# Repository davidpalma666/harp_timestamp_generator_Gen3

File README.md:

# Harp Timestamp Generator Gen3

This device generates programable timestamps to up to 6 harp devices.

Includes an internal battery to increase reliability for long term experiments.

# Licensing

The code, designs, documentation, and photos available in this repository is free: you can redistribute it and/or modify it under the terms of the used license.
Each subdirectory will contain a license or, possibly, a set of licenses if it involves both hardware and software. Check files named LICENSE.

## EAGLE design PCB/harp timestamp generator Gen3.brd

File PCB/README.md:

# Harp Timestamp Generator Gen1

## Licensing

The designs, documentation, and photos available in this repository are free: you can redistribute it and/or modify it under the terms of the used license.
Check file named LICENSE.

Copyright OEPS 2021

<br />This work is licensed under a <a rel="license" href="http://creativecommons.org/licenses/by-nc-sa/3.0/igo/">Creative Commons Attribution-NonCommercial-ShareAlike 3.0 IGO License</a>.

If your are interested in obtaining a license to sell this device, please contact info@oeps.tech

[1]: https://docs.google.com/spreadsheets/d/1aobmmEzBDethzIlrm1eg0eYkBqlyX3s9WbA9KgRwVQI/edit?usp=sharing

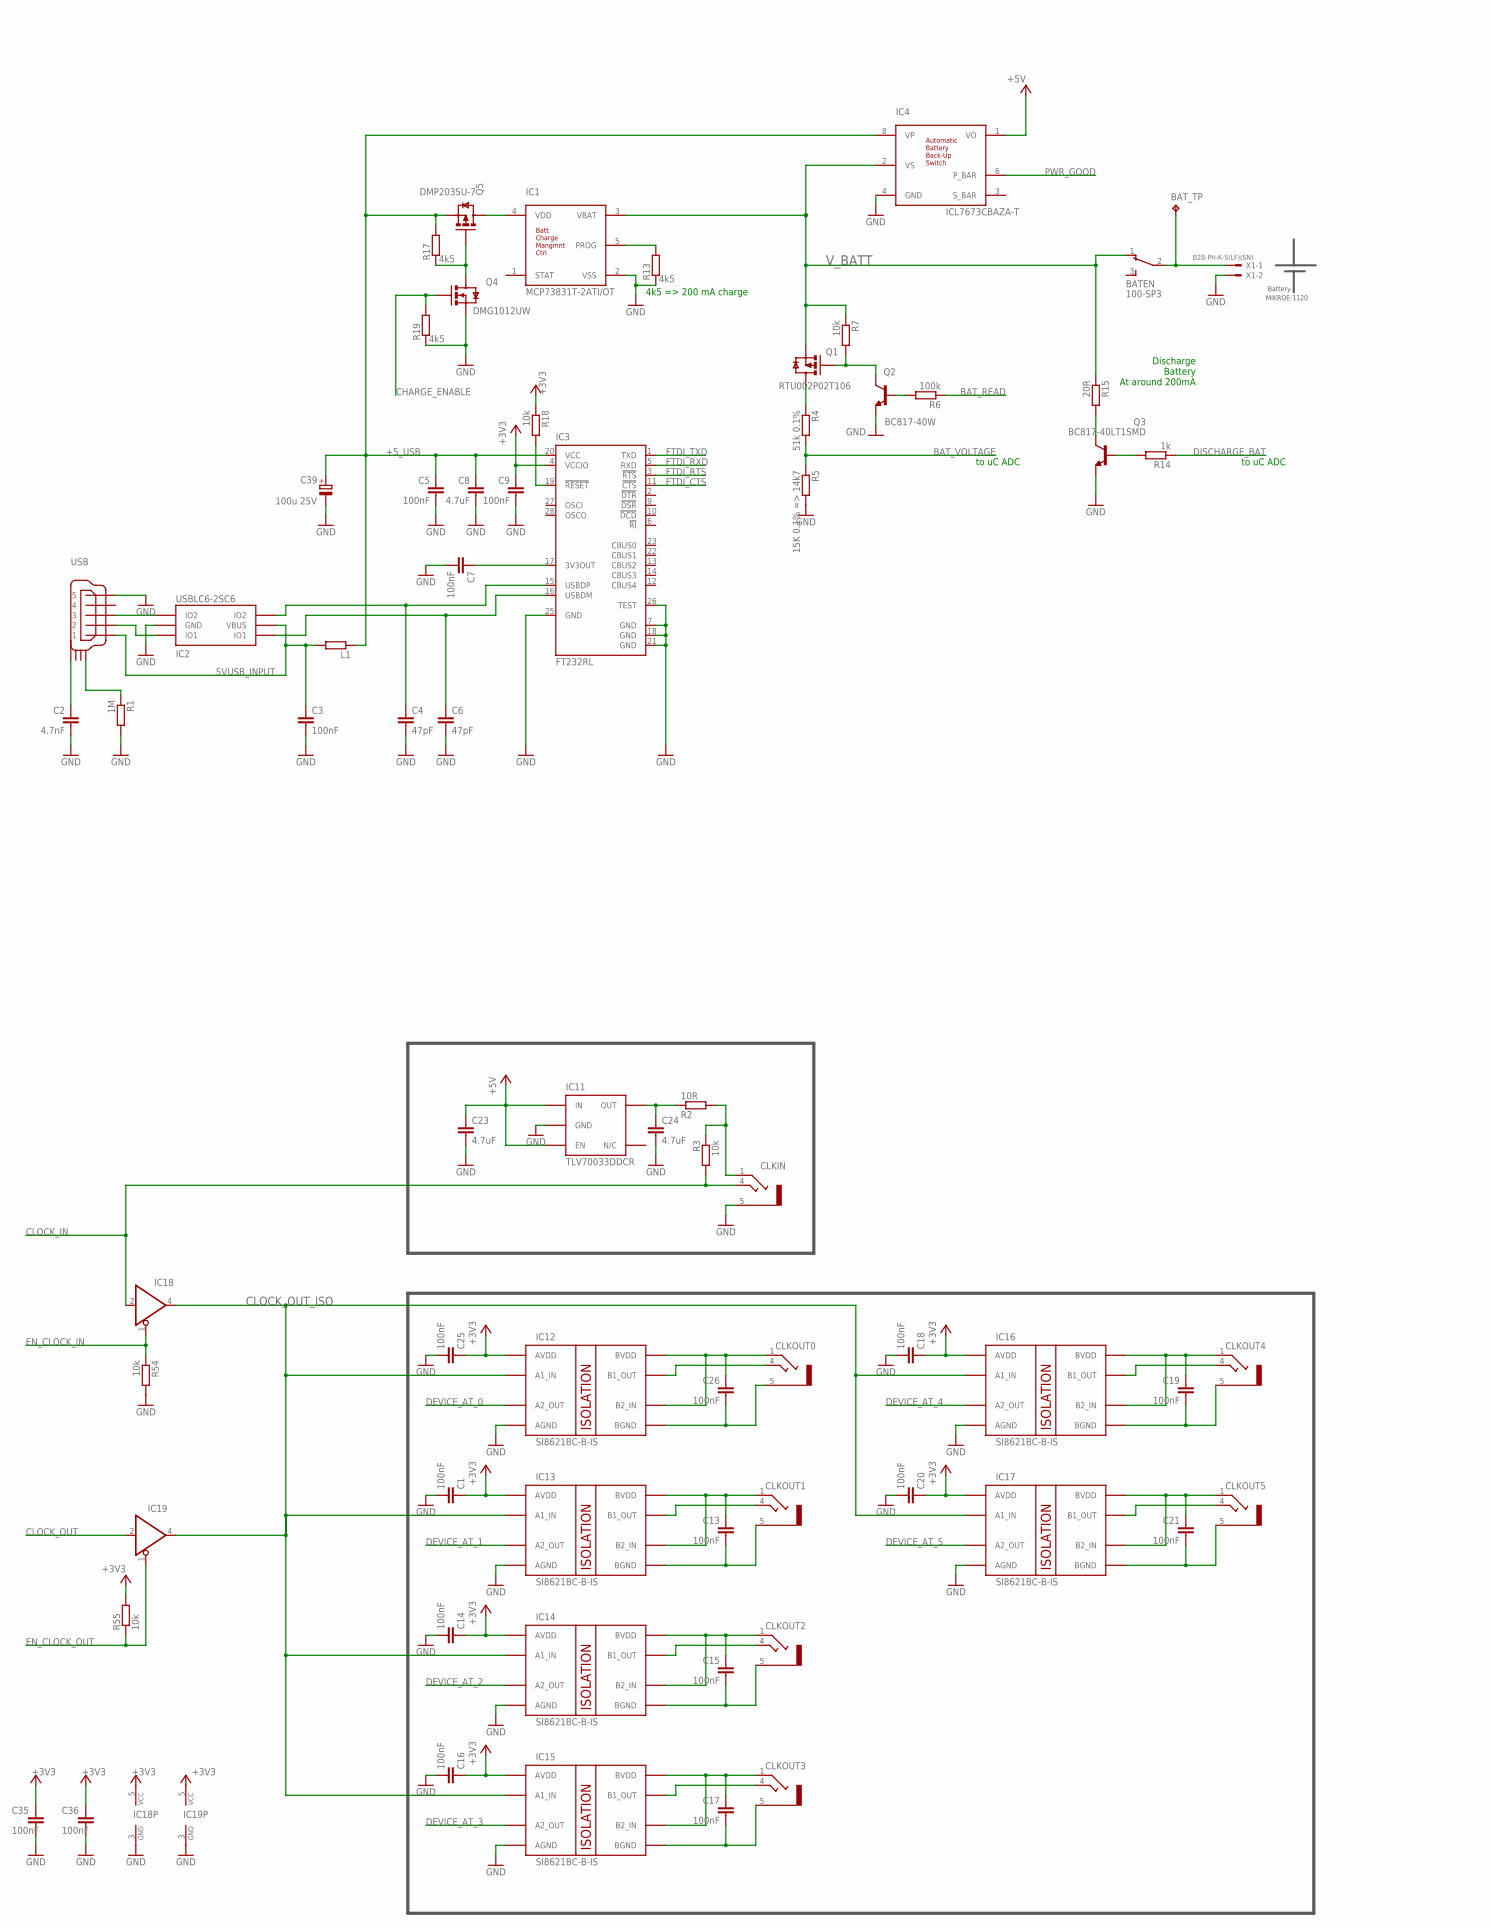
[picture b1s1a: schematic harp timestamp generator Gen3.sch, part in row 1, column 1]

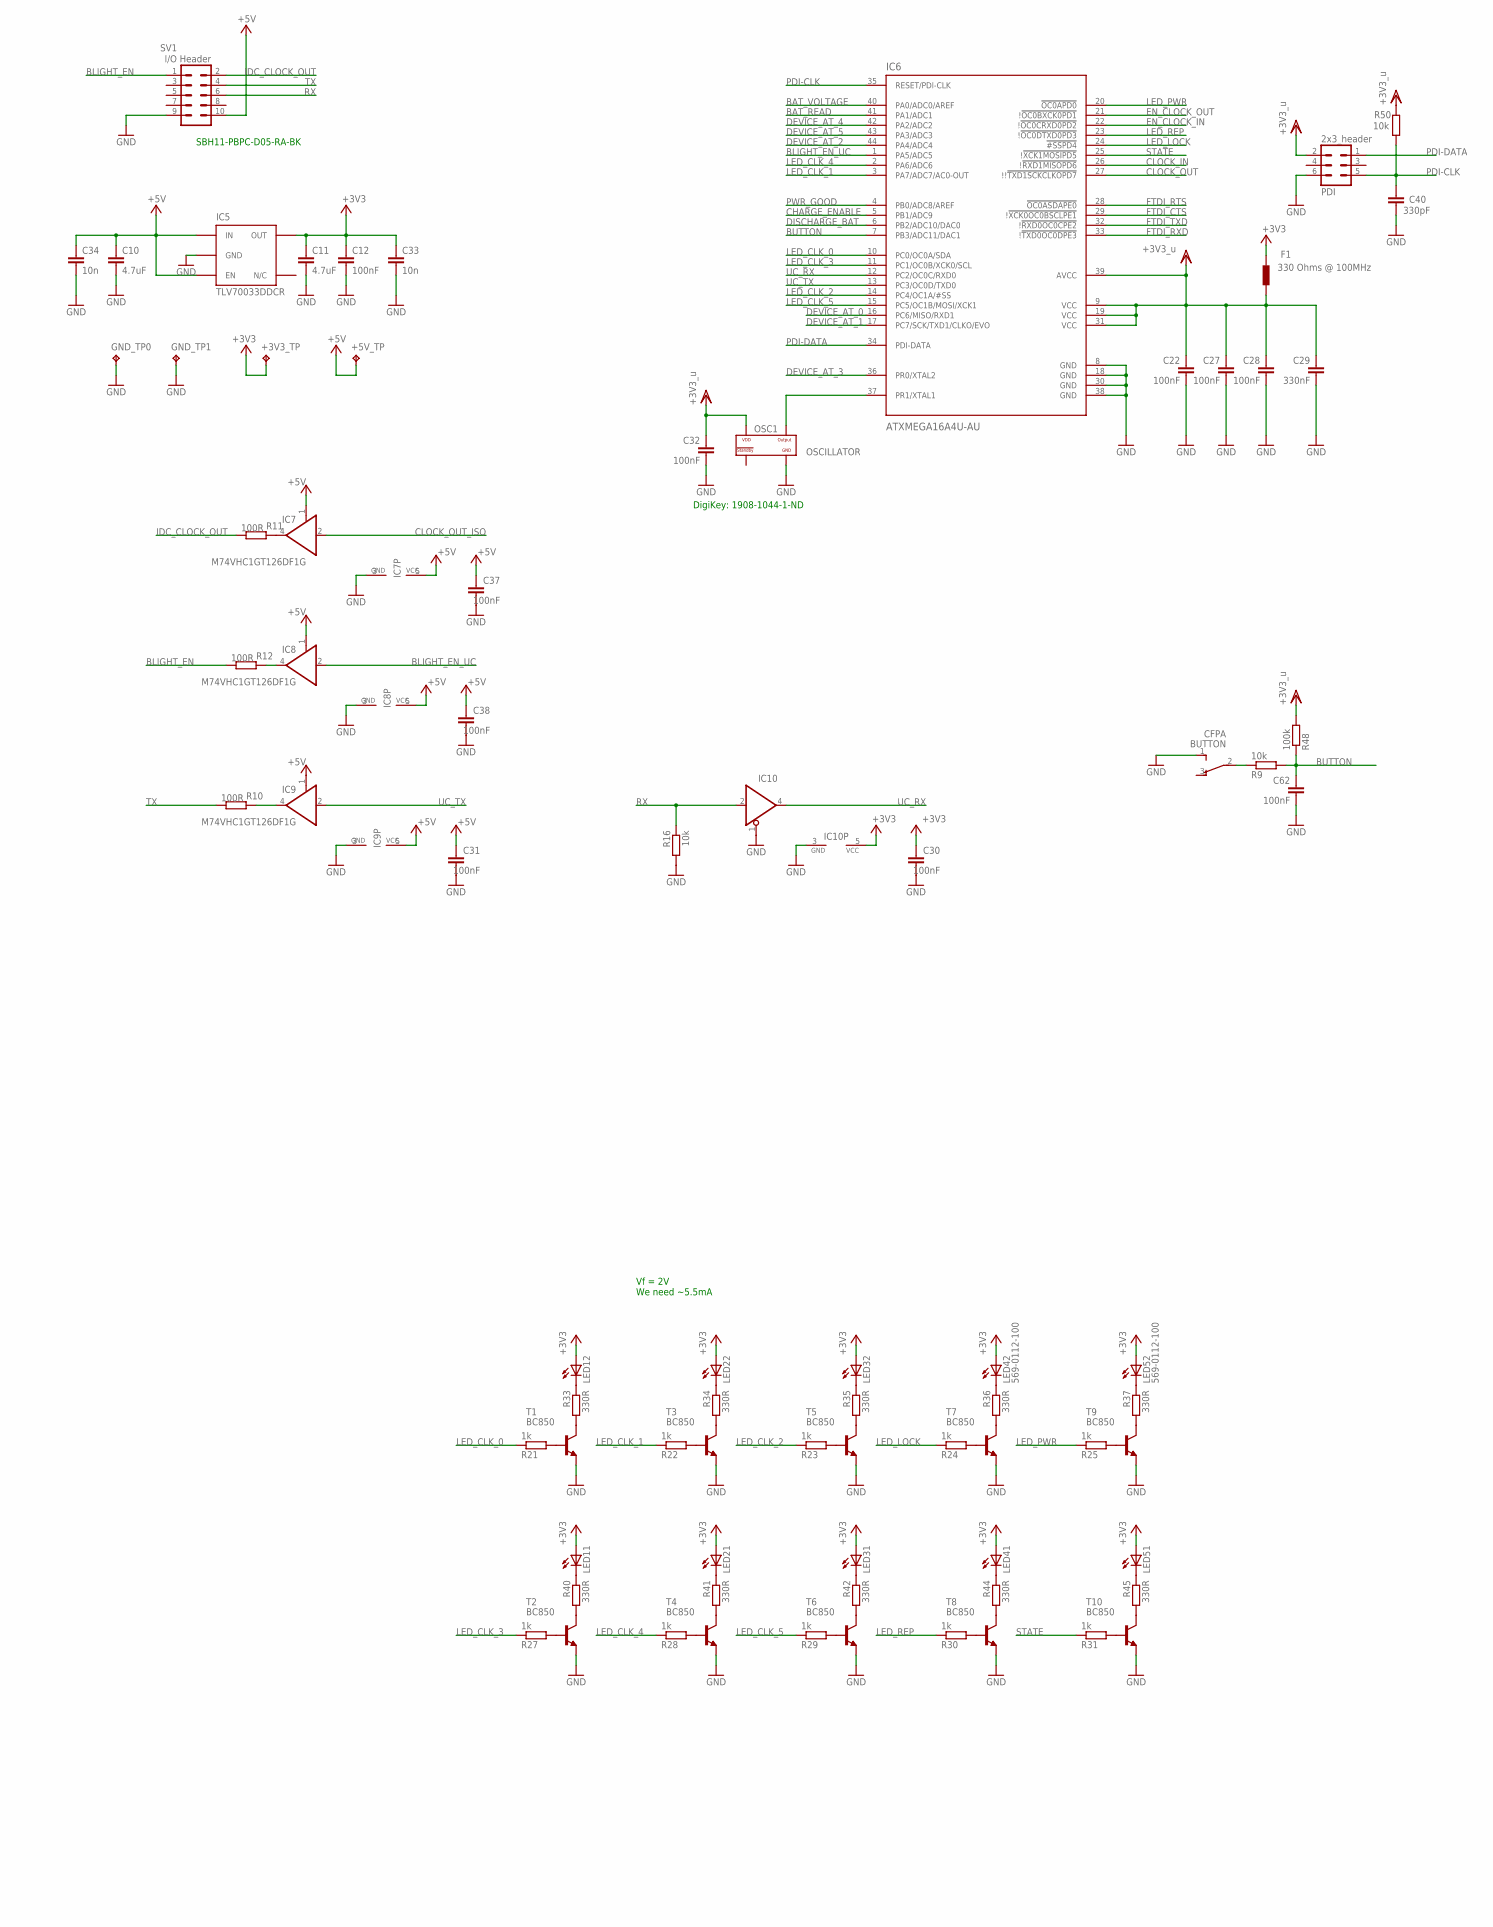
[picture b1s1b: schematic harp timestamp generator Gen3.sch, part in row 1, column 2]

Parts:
+3V3_TP, +5V_TP: TPPAD1-13; P1-13; MPN n.a.
BATEN: 100-SP3; 2M1-SP1-T2-B4-M6RE
BAT_TP: TPPAD1-13; P1-13; MPN n.a.
BUTTON: CFPA; MPN CFPA-1FB4-A2T
C1, C3, C5, C7, C9, C12, C13, C14, C15, C16, C17, C18, C19, C20, C21, C22, C25, C26, C27, C28, C30, C31, C32, C35, C36, C37, C38, C62: 100nF; C0402; MPN CGA2B3X7R1H104K050BB
C2: 4.7nF; C0402; MPN UMK105B7472KV-F
C4, C6: 47pF; C0402; MPN 04025A470JAT2A
C8, C10, C11, C23, C24: 4.7uF; C0603; MPN EMK107ABJ475KA-T
C29: 330nF; C0402; MPN GRM155R61A334KE15D
C33, C34: 10n; C0402; MPN CL05B103KB5NNNC
C39: 100u 25V; TT2D6; MPN EEUFM1E101B
C40: 330pF; C0402; MPN C0402C331J5GACTU
CLKIN: CLCK_JACK; 35RASMT2BHNTRX; MPN 35RASMT2BHNTRX
CLKOUT0, CLKOUT1, CLKOUT2, CLKOUT3, CLKOUT4, CLKOUT5: CLCK_JACK; 35RASMT2BHNTRX; MPN 35RASMT2BHNTRX
F1: 330 Ohms @ 100MHz; R0603; MPN BLM18SG331TN1D
GND_TP0, GND_TP1: TPPAD1-13; P1-13; MPN n.a.
IC1: MCP73831T-2ATI/OT; TSOT23-5
IC2: USBLC6-2SC6; SOT23-6L; MPN USBLC6-2SC6
IC3: FT232RL; SSOP28; MPN FT232RL-REEL
IC4: ICL7673CBAZA-T; SOIC8; MPN ICL7673CBAZA-T
IC5, IC11: TLV70033DDCR; TSOT23-5; MPN TLV70033DDCR
IC6: ATXMEGA16A4U-AU; QFP80P1200X1200X120-44N; MPN ATXMEGA16A4U-AU
IC7, IC8, IC9: M74VHC1GT126DF1G; SC70-5; MPN M74VHC1GT126DF1G
IC10, IC18, IC19: SN74LVC1G125DBVT; SOT23-5; MPN SN74LVC1G125DBVT
IC12, IC13, IC14, IC15, IC16, IC17: SI8621BC-B-IS; SOIC8; MPN Si8621BC-B-IS
L1: 40R@100MHz; R0805; MPN MI0805K400R-10
LED1, LED2, LED3, LED4, LED5: 569-0112-100; 569-011X-X00_LED_ARRAY; MPN 5690-111-100F
OSC1: OSCILLATOR; OSCILLATOR_3.2X2.5; MPN O 32,0-JT32C-A-K-3,3-LF
PDI: 2x3_header; MA03-2; MPN 67996-206HLF
Q1: RTU002P02T106; SOT323; MPN RTU002P02T106
Q2: BC817-40W; SOT323-BEC; MPN BC817-40W,135
Q3: BC817-40LT1SMD; SOT23-BEC; MPN SBC817-40LT1G
Q4: DMG1012UW; SOT323; MPN DMG1012UW-7
Q5: DMP2035U-7; SOT323
R1: 1M; R0402; MPN CRCW04021M00FKEDC
R2: 10R; R0402; MPN CRCW040210R0FKEDHP
R3, R7, R9, R16, R18: 10k; R0402; MPN CRCW040210K0FKEDC
R4: 51k 0.1%; R0402; MPN ERA-2AEB513X
R5: 15K 0.1% => 14k7; R0402; MPN RT0402BRD0714K7L
R6, R48: 100k; R0402; MPN ERJ-2RHD1002X
R10, R11, R12: 100R; R0603; MPN RT0603DRD07100RL
R13, R17, R19: 4k5; R0402; MPN RT0402BRD074K53L
R14: 1k; R0402; MPN CRCW040210K0FKEDC
R15: 20R; R2512; MPN RCP2512W25R0GEB
R21, R22, R23, R24, R25, R27, R28, R29, R30, R31: 1k; R0402; MPN CRCW04021K00FKEDHP
R33, R34, R35, R36, R37, R40, R41, R42, R44, R45: 330R; R0402; MPN RC0402FR-07330RL
R50: 10k; R0402; MPN CRCW040210K0FKED
R54, R55: 10k; R0402; MPN CRCW04021K00FKEDHP
SV1: I/O Header; ML10L; MPN SBH11-PBPC-D05-RA-BK
T1, T2, T3, T4, T5, T6, T7, T8, T9, T10: BC850; SOT23; MPN BC850C,215
USB: mini USB; 240-0002-1; MPN UX60-MB-5S8
X1: B2B-PH-K-S(LF)(SN); JST-XH-02-PACKAGE-ROUND-PAD; MPN B2B-PH-K-S(LF)(SN)

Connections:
5VUSB_INPUT: C3.1, IC2.P$5 (VBUS), L1.2, USB.P$1 (1)
+3V3: +3V3_TP.TP, C1.1, C9.1, C11.1, C12.1, C14.1, C16.1, C18.1, C20.1, C25.1, C30.1, C33.1, C35.1, C36.1, F1.2, IC3.4 (VCCIO), IC5.5 (OUT), IC10.5 (VCC), IC12.1 (AVDD), IC13.1 (AVDD), IC14.1 (AVDD), IC15.1 (AVDD), IC16.1 (AVDD), IC17.1 (AVDD), IC18.5 (VCC), IC19.5 (VCC), LED1.A1 (A), LED1.A2 (A), LED2.A1 (A), LED2.A2 (A), LED3.A1 (A), LED3.A2 (A), LED4.A1 (A), LED4.A2 (A), LED5.A1 (A), LED5.A2 (A), R18.1, R55.2
+5V: +5V_TP.TP, C10.1, C23.1, C31.1, C34.1, C37.1, C38.1, IC4.1 (VO), IC5.1 (IN), IC5.3 (EN), IC7.1 (OE), IC7.5 (VCC), IC8.1 (OE), IC8.5 (VCC), IC9.1 (OE), IC9.5 (VCC), IC11.1 (IN), IC11.3 (EN), SV1.10
+5_USB: C5.1, C8.1, C39.+, IC3.20 (VCC), IC4.8 (VP), L1.1, Q5.1 (S), R17.2
BAT_READ: IC6.41 (PA1/ADC1), R6.1
BAT_VOLTAGE: IC6.40 (PA0/ADC0/AREF), R4.2, R5.1
BLIGHT_EN: R12.1, SV1.1
BLIGHT_EN_UC: IC6.1 (PA5/ADC5), IC8.2 (I)
BUTTON: C62.1, IC6.7 (PB3/ADC11/DAC1), R9.2, R48.1
CHARGE_ENABLE: IC6.5 (PB1/ADC9), Q4.2 (G), R19.2
CLKOUT0: CLKOUT0.4, IC12.7 (B1_OUT)
CLKOUT1: CLKOUT1.4, IC13.7 (B1_OUT)
CLKOUT2: CLKOUT2.4, IC14.7 (B1_OUT)
CLKOUT3: CLKOUT3.4, IC15.7 (B1_OUT)
CLKOUT4: CLKOUT4.4, IC16.7 (B1_OUT)
CLKOUT5: CLKOUT5.4, IC17.7 (B1_OUT)
CLOCK_IN: CLKIN.4, IC6.26 (!!RXD1MISOPD6), IC18.2 (I), R3.2
CLOCK_OUT: IC6.27 (!!!TXD1SCKCLKOPD7), IC19.2 (I)
CLOCK_OUT_ISO: IC7.2 (I), IC12.2 (A1_IN), IC13.2 (A1_IN), IC14.2 (A1_IN), IC15.2 (A1_IN), IC16.2 (A1_IN), IC17.2 (A1_IN), IC18.4 (O), IC19.4 (O)
DEVICE_AT_0: IC6.16 (PC6/MISO/RXD1), IC12.3 (A2_OUT)
DEVICE_AT_1: IC6.17 (PC7/SCK/TXD1/CLKO/EVO), IC13.3 (A2_OUT)
DEVICE_AT_2: IC6.44 (PA4/ADC4), IC14.3 (A2_OUT)
DEVICE_AT_3: IC6.36 (PR0/XTAL2), IC15.3 (A2_OUT)
DEVICE_AT_4: IC6.42 (PA2/ADC2), IC16.3 (A2_OUT)
DEVICE_AT_5: IC6.43 (PA3/ADC3), IC17.3 (A2_OUT)
DISCHARGE_BAT: IC6.6 (PB2/ADC10/DAC0), R14.1
EN_CLOCK_IN: IC6.22 (!!OC0CRXD0PD2), IC18.1 (OE), R54.1
EN_CLOCK_OUT: IC6.21 (!!OC0BXCK0PD1), IC19.1 (OE), R55.1
FTDI_CTS: IC3.11 (!CTS), IC6.29 (!!XCK0OC0BSCLPE1)
FTDI_RTS: IC3.3 (!RTS), IC6.28 (!OC0ASDAPE0)
FTDI_RXD: IC3.5 (RXD), IC6.33 (!!TXD0OC0DPE3)
FTDI_TXD: IC3.1 (TXD), IC6.32 (!!RXD0OC0CPE2)
GND: BUTTON.1 (3), C1.2, C2.2, C3.2, C4.2, C5.2, C6.2, C7.2, C8.2, C9.2, C10.2, C11.2, C12.2, C14.2, C16.2, C18.2, C20.2, C22.2, C23.2, C24.2, C25.2, C27.2, C28.2, C29.2, C30.2, C31.2, C32.2, C33.2, C34.2, C35.2, C36.2, C37.2, C38.2, C39.-, C40.2, C62.2, CLKIN.5, GND_TP0.TP, GND_TP1.TP, IC1.2 (VSS), IC2.P$2 (GND), IC3.7 (GND), IC3.18 (GND), IC3.21 (GND), IC3.25 (GND), IC3.26 (TEST), IC4.4 (GND), IC5.2 (GND), IC6.8 (GND), IC6.18 (GND), IC6.30 (GND), IC6.38 (GND), IC7.3 (GND), IC8.3 (GND), IC9.3 (GND), IC10.1 (OE), IC10.3 (GND), IC11.2 (GND), IC12.4 (AGND), IC13.4 (AGND), IC14.4 (AGND), IC15.4 (AGND), IC16.4 (AGND), IC17.4 (AGND), IC18.3 (GND), IC19.3 (GND), OSC1.P$2 (GND), PDI.6, Q2.E, Q3.E, Q4.1 (S), R1.2, R5.2, R13.1, R16.2, R19.1, R54.2, SV1.9, T1.2 (E), T2.2 (E), T3.2 (E), T4.2 (E), T5.2 (E), T6.2 (E), T7.2 (E), T8.2 (E), T9.2 (E), T10.2 (E), USB.P$5 (5), X1.2
GND_ISO: C26.2, CLKOUT0.5, IC12.5 (BGND)
GND_ISO1: C13.2, CLKOUT1.5, IC13.5 (BGND)
GND_ISO2: C15.2, CLKOUT2.5, IC14.5 (BGND)
GND_ISO3: C17.2, CLKOUT3.5, IC15.5 (BGND)
GND_ISO4: C19.2, CLKOUT4.5, IC16.5 (BGND)
GND_ISO5: C21.2, CLKOUT5.5, IC17.5 (BGND)
IDC_CLOCK_OUT: R11.1, SV1.2
LED_CLK_0: IC6.10 (PC0/OC0A/SDA), R21.1
LED_CLK_1: IC6.3 (PA7/ADC7/AC0-OUT), R22.1
LED_CLK_2: IC6.14 (PC4/OC1A/#SS), R23.1
LED_CLK_3: IC6.11 (PC1/OC0B/XCK0/SCL), R27.1
LED_CLK_4: IC6.2 (PA6/ADC6), R28.1
LED_CLK_5: IC6.15 (PC5/OC1B/MOSI/XCK1), R29.1
LED_LOCK: IC6.24 (!#SSPD4), R24.1
LED_PWR: IC6.20 (!OC0APD0), R25.1
LED_REP: IC6.23 (!!OC0DTXD0PD3), R30.1
unnamed: R24.2, T7.1 (B)
unnamed: Q4.3 (D), Q5.2 (G), R17.1
unnamed: IC8.4 (O), R12.2
unnamed: IC9.4 (O), R10.2
unnamed: C26.1, CLKOUT0.1, IC12.6 (B2_IN), IC12.8 (BVDD)
unnamed: C13.1, CLKOUT1.1, IC13.6 (B2_IN), IC13.8 (BVDD)
unnamed: R36.2, T7.3 (C)
unnamed: IC7.4 (O), R11.2
unnamed: IC1.4 (VDD), Q5.3 (D)
unnamed: C15.1, CLKOUT2.1, IC14.6 (B2_IN), IC14.8 (BVDD)
unnamed: R22.2, T3.1 (B)
unnamed: IC1.5 (PROG), R13.2
unnamed: R21.2, T1.1 (B)
unnamed: LED3.C1 (C), R42.1
unnamed: R33.2, T1.3 (C)
unnamed: R27.2, T2.1 (B)
unnamed: R34.2, T3.3 (C)
unnamed: R40.2, T2.3 (C)
unnamed: LED3.C2 (C), R35.1
unnamed: R28.2, T4.1 (B)
unnamed: R41.2, T4.3 (C)
unnamed: R23.2, T5.1 (B)
unnamed: R35.2, T5.3 (C)
unnamed: R29.2, T6.1 (B)
unnamed: R42.2, T6.3 (C)
unnamed: LED1.C2 (C), R33.1
unnamed: LED2.C2 (C), R34.1
unnamed: LED1.C1 (C), R40.1
unnamed: LED2.C1 (C), R41.1
unnamed: R30.2, T8.1 (B)
unnamed: Q3.B, R14.2
unnamed: Q3.C, R15.2
unnamed: C17.1, CLKOUT3.1, IC15.6 (B2_IN), IC15.8 (BVDD)
unnamed: C7.1, IC3.17 (3V3OUT)
unnamed: IC2.P$1 (IO1), USB.P$2 (2)
unnamed: CLKIN.1, R2.2, R3.1
unnamed: C24.1, IC11.5 (OUT), R2.1
unnamed: BUTTON.2, R9.1
unnamed: C19.1, CLKOUT4.1, IC16.6 (B2_IN), IC16.8 (BVDD)
unnamed: R44.2, T8.3 (C)
unnamed: C21.1, CLKOUT5.1, IC17.6 (B2_IN), IC17.8 (BVDD)
unnamed: IC2.P$3 (IO2), USB.P$3 (3)
unnamed: R25.2, T9.1 (B)
unnamed: R37.2, T9.3 (C)
unnamed: R31.2, T10.1 (B)
unnamed: C2.1, USB.SHIELD_4
unnamed: R45.2, T10.3 (C)
unnamed: R1.1, USB.SHIELD_1
unnamed: LED5.C1 (C), R45.1
unnamed: LED5.C2 (C), R37.1
unnamed: LED4.C2 (C), R36.1
unnamed: LED4.C1 (C), R44.1
unnamed: BATEN.2, BAT_TP.TP, X1.1
unnamed: Q1.3 (D), R4.1
unnamed: Q1.2 (G), Q2.C, R7.2
unnamed: Q2.B, R6.2
unnamed: IC3.19 (!RESET), R18.2
OSC1: IC6.37 (PR1/XTAL1), OSC1.P$3 (OUTPUT)
PDI-CLK: C40.1, IC6.35 (RESET/PDI-CLK), PDI.5, R50.1
PDI-DATA: IC6.34 (PDI-DATA), PDI.1
PWR_GOOD: IC4.6 (P_BAR), IC6.4 (PB0/ADC8/AREF)
RX: IC10.2 (I), R16.1, SV1.6
STATE: IC6.25 (!!XCK1MOSIPD5), R31.1
TX: R10.1, SV1.4
UC_RX: IC6.12 (PC2/OC0C/RXD0), IC10.4 (O)
UC_TX: IC6.13 (PC3/OC0D/TXD0), IC9.2 (I)
USBDM: C6.1, IC2.P$6 (IO1), IC3.16 (USBDM)
USBDP: C4.1, IC2.P$4 (IO2), IC3.15 (USBDP)
VDD: C22.1, C27.1, C28.1, C29.1, C32.1, F1.1, IC6.9 (VCC), IC6.19 (VCC), IC6.31 (VCC), IC6.39 (AVCC), OSC1.P$4 (VDD), PDI.2, R48.2, R50.2
V_BATT: BATEN.1, IC1.3 (VBAT), IC4.2 (VS), Q1.1 (S), R7.1, R15.1

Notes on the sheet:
Vf = 2V We need ~5.5mA
SBH11-PBPC-D05-RA-BK
4k5 => 200 mA charge
Battery
to uC ADC
MIKROE-1120
Discharge Battery At around 200mA
DigiKey: 1908-1044-1-ND

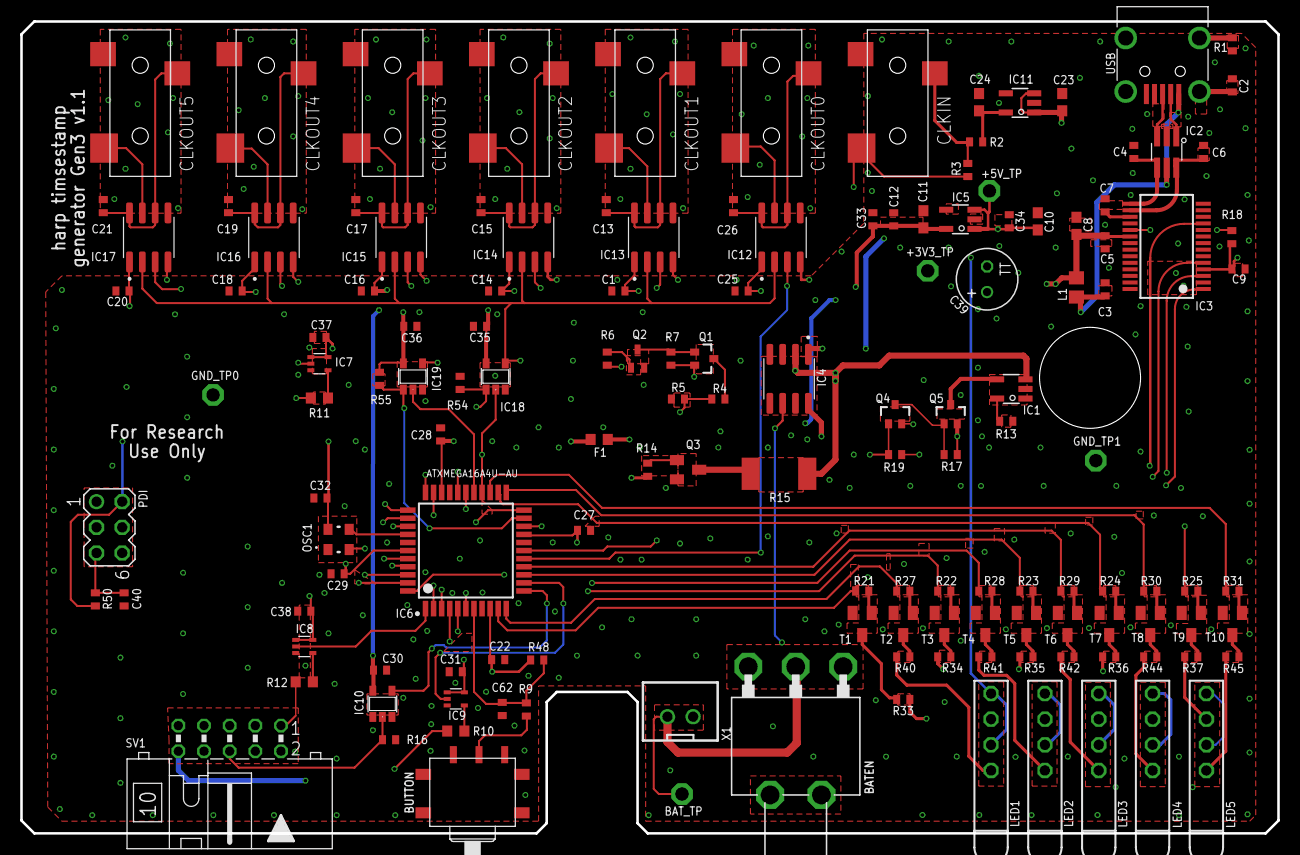
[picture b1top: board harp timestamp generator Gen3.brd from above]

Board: 4 copper layers, 124.5 x 80.4 mm, 143 parts (0 on the bottom side), 119 nets.

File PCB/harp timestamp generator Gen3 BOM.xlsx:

Qty | Value | Package | Parts | MPN | Type | Distributor | Distributor PN
ASSEMBLY HOUSE
1 | CFPA | CFPA | BUTTON | CFPA-1FB4-A2T | SMD | Digikey | 563-1246-1-ND
28 | 100nF | C0402 | C1, C3, C5, C7, C9, C12, C13, C14, C15, C16, C17, C18, C19, C20, C21, C22, C25,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 | CGA2B3X7R1H104K050BB | SMD | Digikey | 445-6899-1-ND
5 | 4.7uF | C0603 | C8, C10, C11, C23, C24 | CRCW040210R0FKEDHP | SMD | Digikey | 541-10.0YCT-ND
1 | 4.7nF | C0402 | C2 | UMK105B7472KV-F | SMD | Digikey | 587-2237-1-ND
1 | 330nF | C0402 | C29 | GRM155R61A334KE15D | SMD | Digikey | 490-3263-1-ND
2 | 10n | C0402 | C33, C34 | CL05B103KB5NNNC | SMD | Digikey | 1276-1028-1-ND
2 | 47pF | C0402 | C4, C6 | 06035A470JAT2A | SMD | Digikey | 478-1171-1-ND
1 | 100u 25V | TT2D6 | C39 | EEUFM1E101B | TH | Digikey | P19702CT-ND
1 | 330pF | C0402 | C40 | C0402C331J5GACTU | SMD | Digikey | 399-7787-1-ND
7 | CLCK_JACK | 35RASMT2BHNTRX | CLKIN, CLKOUT0, CLKOUT1, CLKOUT2, CLKOUT3, CLKOUT4, CLKOUT5 | 35RASMT2BHNTRX | SMD | Digikey | SC1489-1-ND
1 | 330 Ohms @ 100MHz | R0603 | F1 | BLM18SG331TN1D | SMD | Digikey | 490-3997-1-ND
1 | MCP73831T-2ATI/OT | TSOT23-5 | IC1 | MCP73831T-2ATI/OT | SMD | Digikey | MCP73831T-2ATI/OTCT-ND
3 | SN74LVC1G125DBVT | SOT23-5 | IC10, IC18, IC19 | SN74LVC1G125DBVT | SMD | Digikey | 296-26595-1-ND
6 | SI8621BC-B-IS | SOIC8 | IC12, IC13, IC14, IC15, IC16, IC17 | Si8621BC-B-IS | SMD | Digikey | 336-2064-5-ND | Replacements: SI8621BB-B-IS
1 | USBLC6-2SC6 | SOT23-6L | IC2 | USBLC6-2SC6 | SMD | Digikey | 497-5235-1-ND
1 | FT232RL | SSOP28 | IC3 | FT232RL-REEL | SMD | Digikey | 768-1007-1-ND
1 | ICL7673CBAZA-T | SOIC8 | IC4 | ICL7673CBAZA-T | SMD | Digikey | ICL7673CBAZA-TCT-ND
2 | TLV70033DDCR | TSOT23-5 | IC5, IC11 | TLV70033DDCR | SMD | Digikey | 296-27937-6-ND
1 | ATXMEGA16A4U-AU | QFP80P1200X1200X120-44N | IC6 | ATXMEGA16A4U-AU | SMD | Digikey | ATXMEGA16A4U-AU-ND
3 | M74VHC1GT126DF1G | SC70-5 | IC7, IC8, IC9 | M74VHC1GT126DF1G | SMD | Digikey | M74VHC1GT126DF1GOSCT-ND
1 | 40R@100MHz | R0805 | L1 | MI0805K400R-10 | SMD | Digikey | 240-2389-1-ND
5 | 569-0112-100 | 569-011X-X00_LED_ARRAY | LED1, LED2, LED3, LED4, LED5 | 5690-111-100F | SMD | Digikey | 350-1782-ND
1 | OSCILLATOR | OSCILLATOR_3.2X2.5 | OSC1 | O 32,0-JT32C-A-K-3,3-LF | SMD | Digikey | 1908-1044-1-ND
1 | 2x3_header | MA03-2 | PDI | 67996-206HLF | TH | Digikey | 609-3210-ND
1 | RTU002P02T106 | SOT323 | Q1 | RTU002P02T106 | SMD | Digikey | RTU002P02T106CT-ND
1 | BC817-40W | SOT323-BEC | Q2 | BC817-40W,135 | SMD | Digikey | 1727-6185-1-ND
1 | BC817-40LT1SMD | SOT23-BEC | Q3 | SBC817-40LT1G | SMD | Digikey | SBC817-40LT1GOSCT-ND
1 | DMG1012UW | SOT323 | Q4 | DMG1012UW-7 | SMD | Digikey | DMG1012UW-7DICT-ND
1 | DMP2035U-7 | SOT323 | Q5 | DMP2035U-7 | SMD | Digikey | DMP2035U-7DICT-ND
1 | 1M | R0402 | R1 | CRCW04021M00FKEDC | SMD | Digikey | DMP2035U-7
3 | 100R | R0603 | R10, R11, R12 | RT0603DRD07100RL | SMD | Digikey | 311-100DCT-ND
3 | 4k5 | R0402 | R13, R17, R19 | RT0402BRD074K53L | SMD | Digikey | YAG1444CT-ND
1 | 20R | R2512 | R15 | CRM2512-FX-20R0ELF | SMD | Digikey | 118-CRM2512-FX-20R0ELFCT-ND
1 | 10R | R0402 | R2 | CRCW040210R0FKEDHP | SMD | Digikey | 541-10.0YCT-ND
13 | 1k | R0402 | R14, R21, R22, R23, R24, R25, R27, R28, R29, R30, R31, R54, R55 | CRCW04021K00FKED | SMD | Digikey | 541-1.00KYCT-ND
6 | 10k | R0402 | R3, R7, R9, R16, R18, R50 | CRCW040210K0FKEDC | SMD | Digikey | 541-3959-1-ND
10 | 330R | R0402 | R33, R34, R35, R36, R37, R40, R41, R42, R44, R45 | RC0402FR-07330RL | SMD | Digikey | 311-330LRCT-ND
1 | 51k 0.1% | R0402 | R4 | ERA-2AEB513X | SMD | Digikey | P51KDCCT-ND
1 | 15K 0.1% => 14k7 | R0402 | R5 | RT0402BRD0714K7L | SMD | Digikey | YAG4174CT-ND
2 | 100k | R0402 | R6, R48 | RC0603FR-07100KL | SMD | Digikey | 311-100KHRCT-ND
1 | 0 | R0402 | R8 | RC0603FR-070RL | SMD | Digikey | 311-0.0HRCT-ND
1 | I/O Header | ML10L | SV1 | SBH11-PBPC-D05-RA-BK | TH | Digikey | S9177-ND
10 | BC850 | SOT23 | T1, T2, T3, T4, T5, T6, T7, T8, T9, T10 | BC850C,215 | SMD | Digikey | 1727-4862-1-ND
1 | mini USB | 240-0002-1 | USB | UX60-MB-5S8 | SMD | Digikey | H2960TR-ND
1 | B2B-PH-K-S(LF)(SN) | JST-XH-02-PACKAGE-ROUND-PAD | X1 | B2B-XH-A(LF)(SN) | SMD | Digikey | 455-2247-ND
POST-PRODUCTION
1 |  |  | Front Panel PCB | PCBWAY
1 |  |  | Rear Panel PCB | PCBWAY
1 |  |  | Enclosure | B5-080BK
1 |  |  | Battery lithium Polymer 2 Ah | MIKROE-1120 | - | Farnell | 2786900
4 |  |  | Bumper Cylindrical Dome 9.53mm | SJ-5306-CLEAR-3000/CASE
ACCESSORIES
3 |  |  | 3.5mm stereo jack cable 0.3 m, Black | P312-001 | - | Digikey | TL1621-ND
4 |  |  | 3.5mm stereo jack cable 1.2 m, Black | AV13646 |  | Farnell | 3712278
1 |  |  | 0.9 left angle USB cable | USB2HABM3RA |  | Farnell | 3402895
NOTES
 |  |  |  | Number of unique parts | 46
 |  |  |  | Number of SMD parts | 43
 |  |  |  | Number of TH parts | 3

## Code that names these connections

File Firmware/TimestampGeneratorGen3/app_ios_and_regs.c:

#include <avr/io.h>
#include "hwbp_core_types.h"
#include "app_ios_and_regs.h"

/************************************************************************/
/* Configure and initialize IOs                                         */
/************************************************************************/
void init_ios(void)
{	/* Configure input pins */
	io_pin2in(&PORTA, 2, PULL_IO_TRISTATE, SENSE_IO_NO_INT_USED);        // DEVICE_AT_4
	io_pin2in(&PORTA, 3, PULL_IO_TRISTATE, SENSE_IO_NO_INT_USED);        // DEVICE_AT_5
	io_pin2in(&PORTA, 4, PULL_IO_TRISTATE, SENSE_IO_NO_INT_USED);        // DEVICE_AT_2
	io_pin2in(&PORTB, 0, PULL_IO_UP, SENSE_IO_EDGES_BOTH);               // POWER_GOOD
	io_pin2in(&PORTB, 3, PULL_IO_TRISTATE, SENSE_IO_EDGES_BOTH);         // BUTTON
	io_pin2in(&PORTC, 6, PULL_IO_TRISTATE, SENSE_IO_NO_INT_USED);        // DEVICE_AT_0
	io_pin2in(&PORTC, 7, PULL_IO_TRISTATE, SENSE_IO_NO_INT_USED);        // DEVICE_AT_1
	io_pin2in(&PORTR, 0, PULL_IO_TRISTATE, SENSE_IO_NO_INT_USED);        // DEVICE_AT_3

	/* Configure input interrupts */
	io_set_int(&PORTB, INT_LEVEL_LOW, 0, (1<<0), false);                 // POWER_GOOD

	/* Configure output pins */
	io_pin2out(&PORTA, 1, OUT_IO_DIGITAL, IN_EN_IO_EN);                  // BAT_READ
	io_pin2out(&PORTA, 5, OUT_IO_DIGITAL, IN_EN_IO_EN);                  // EN_SCREEN_BACKLIGHT
	io_pin2out(&PORTA, 6, OUT_IO_DIGITAL, IN_EN_IO_EN);                  // LED_CLK_4
	io_pin2out(&PORTA, 7, OUT_IO_DIGITAL, IN_EN_IO_EN);                  // LED_CLK_1
	io_pin2out(&PORTB, 1, OUT_IO_DIGITAL, IN_EN_IO_EN);                  // EN_CHARGE
	io_pin2out(&PORTB, 2, OUT_IO_DIGITAL, IN_EN_IO_EN);                  // EN_DISCHARGE
	io_pin2out(&PORTC, 0, OUT_IO_DIGITAL, IN_EN_IO_EN);                  // LED_CLK_0
	io_pin2out(&PORTC, 1, OUT_IO_DIGITAL, IN_EN_IO_EN);                  // LED_CLK_3
	io_pin2out(&PORTC, 4, OUT_IO_DIGITAL, IN_EN_IO_EN);                  // LED_CLK_2
	io_pin2out(&PORTC, 5, OUT_IO_DIGITAL, IN_EN_IO_EN);                  // LED_CLK_5
	io_pin2out(&PORTD, 0, OUT_IO_DIGITAL, IN_EN_IO_EN);                  // LED_POWER
	io_pin2out(&PORTD, 1, OUT_IO_DIGITAL, IN_EN_IO_EN);                  // EN_CLOCK_OUT
	io_pin2out(&PORTD, 2, OUT_IO_DIGITAL, IN_EN_IO_EN);                  // EN_CLOCK_IN
	io_pin2out(&PORTD, 3, OUT_IO_DIGITAL, IN_EN_IO_EN);                  // LED_REPEATER
	io_pin2out(&PORTD, 4, OUT_IO_DIGITAL, IN_EN_IO_EN);                  // LED_LOCK
	io_pin2out(&PORTD, 5, OUT_IO_DIGITAL, IN_EN_IO_EN);                  // LED_STATE

	/* Initialize output pins */
	clr_BAT_READ;
	clr_EN_SCREEN_BACKLIGHT;
	clr_LED_CLK_4;
	clr_LED_CLK_1;
	clr_EN_CHARGE;
	clr_EN_DISCHARGE;
	clr_LED_CLK_0;
	clr_LED_CLK_3;
	clr_LED_CLK_2;
	clr_LED_CLK_5;
	clr_LED_POWER;
	clr_EN_CLOCK_OUT;
	set_EN_CLOCK_IN;
	clr_LED_REPEATER;
	clr_LED_LOCK;
	clr_LED_STATE;
}

/************************************************************************/
/* Registers' stuff                                                     */
/************************************************************************/
AppRegs app_regs;

uint8_t app_regs_type[] = {
	TYPE_U8,
	TYPE_U8,
	TYPE_U8,
	TYPE_U8,
	TYPE_FLOAT,
	TYPE_FLOAT,
	TYPE_FLOAT,
	TYPE_U16,
	TYPE_U16
};

uint16_t app_regs_n_elements[] = {
	1,
	1,
	1,
	1,
	1,
	1,
	1,
	1,
	1
};

uint8_t *app_regs_pointer[] = {
	(uint8_t*)(&app_regs.REG_CONFIG),
	(uint8_t*)(&app_regs.REG_DEVICES_CONNECTED),
	(uint8_t*)(&app_regs.REG_REPEATER_STATUS),
	(uint8_t*)(&app_regs.REG_BATTERY_RATE),
	(uint8_t*)(&app_regs.REG_BATTERY),
	(uint8_t*)(&app_regs.REG_BATTERY_TH_LOW),
	(uint8_t*)(&app_regs.REG_BATTERY_TH_HIGH),
	(uint8_t*)(&app_regs.REG_BATTERY_CALIBRATION0),
	(uint8_t*)(&app_regs.REG_BATTERY_CALIBRATION1)
};

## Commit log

2021-02-07 Added licenses and READMEs.
2021-02-07 Added the PCB.
2021-02-07 Added auxiliar files.
2021-02-07 Corrected READMEs.
2021-02-08 Corrected buffers' enable.
2021-02-11 Big updates. Very close to final design.
2021-02-11 Added BOM.
2021-02-11 Increased battery current draw to around 250 mA.
2021-02-12 Updated files with the MPN.
2021-02-26 Corrected X1 PN and PCB's orientation.
2021-04-25 Added first firmware files.
2021-04-25 Added an extra 100uF capacitor to +5_USB.
2021-04-25 Added proper filtering to RESET line.
2021-04-28 Corrected the discharge circuit.
2021-05-03 Added replacements.
2021-05-04 Decreased discharge current by ~60 mA to ~175 mA in average.
2021-05-05 Added ability to initiate battery cycle using the external button.
2022-03-30 Removed LOCK from configuration.
2022-03-30 Enhanced shutdown control and visualizers.
2022-03-30 Removed POWER_GOOD and wake up from buttons' interrupts.
2022-04-02 Updated code to harp core 1.10
2022-05-04 Changed battery connection to a new location and added an ON/OFF button.
2022-05-04 Updated BOM and added front and rear panels.
2022-05-04 Updated Bonsai tests workflow and remapped button interrupt.
2022-05-23 Updated front panel to reflect the right device version.
